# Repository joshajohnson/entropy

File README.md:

# Entropy

## A 96% Southpaw keyboard, with split space and encoder support. 

Entropy started as a STM32 powered keyboard running QMK and enclosed in a FR4 and PLA case, but at the time of writing runs on a nRF52 and ZMK, tucked inside a stacked acrylic case.

ZMK enables wireless functionality, and you'll get upwards of 6 months battery life thanks to the 200uA sleep current.

It also supports up to 4 rotary incoders in 5 different positions, along with a myriad of layout options.

## Photos

## Layout
Supports Encoders in (0,0)...(0,3) and (0,19)

ZMK versions only allow 4 encoders to be populated (hiting interrupt limit with 5 encoders)

## Revision History

R0.1: 
- Original STM32 design, no bugs that can't be worked around. 
- Tested and working.

R0.2: 
- Removed overengineering, modified to suit JLCSMT. 
- Fixed plate 2U tight fit. 
- **Has known issues with powering the LEDs, do not use**

### Image of R0.1 and R0.2 Design

R0.3: 

- Moved to nRF52840 and ZMK due to supply issues with the STM32F303 used in R0.1 and R0.2.
- Case design changed to plate mount in stacked acrylic case.
- Design moved to KiCad V6.

R0.4: 
- Battery life and design improvements over R0.3. 
- Few issues requiring rework but suitable for use.

R0.5: 
- Resolved issues found in R0.4, however untested. 
- **Use at your own risk.**

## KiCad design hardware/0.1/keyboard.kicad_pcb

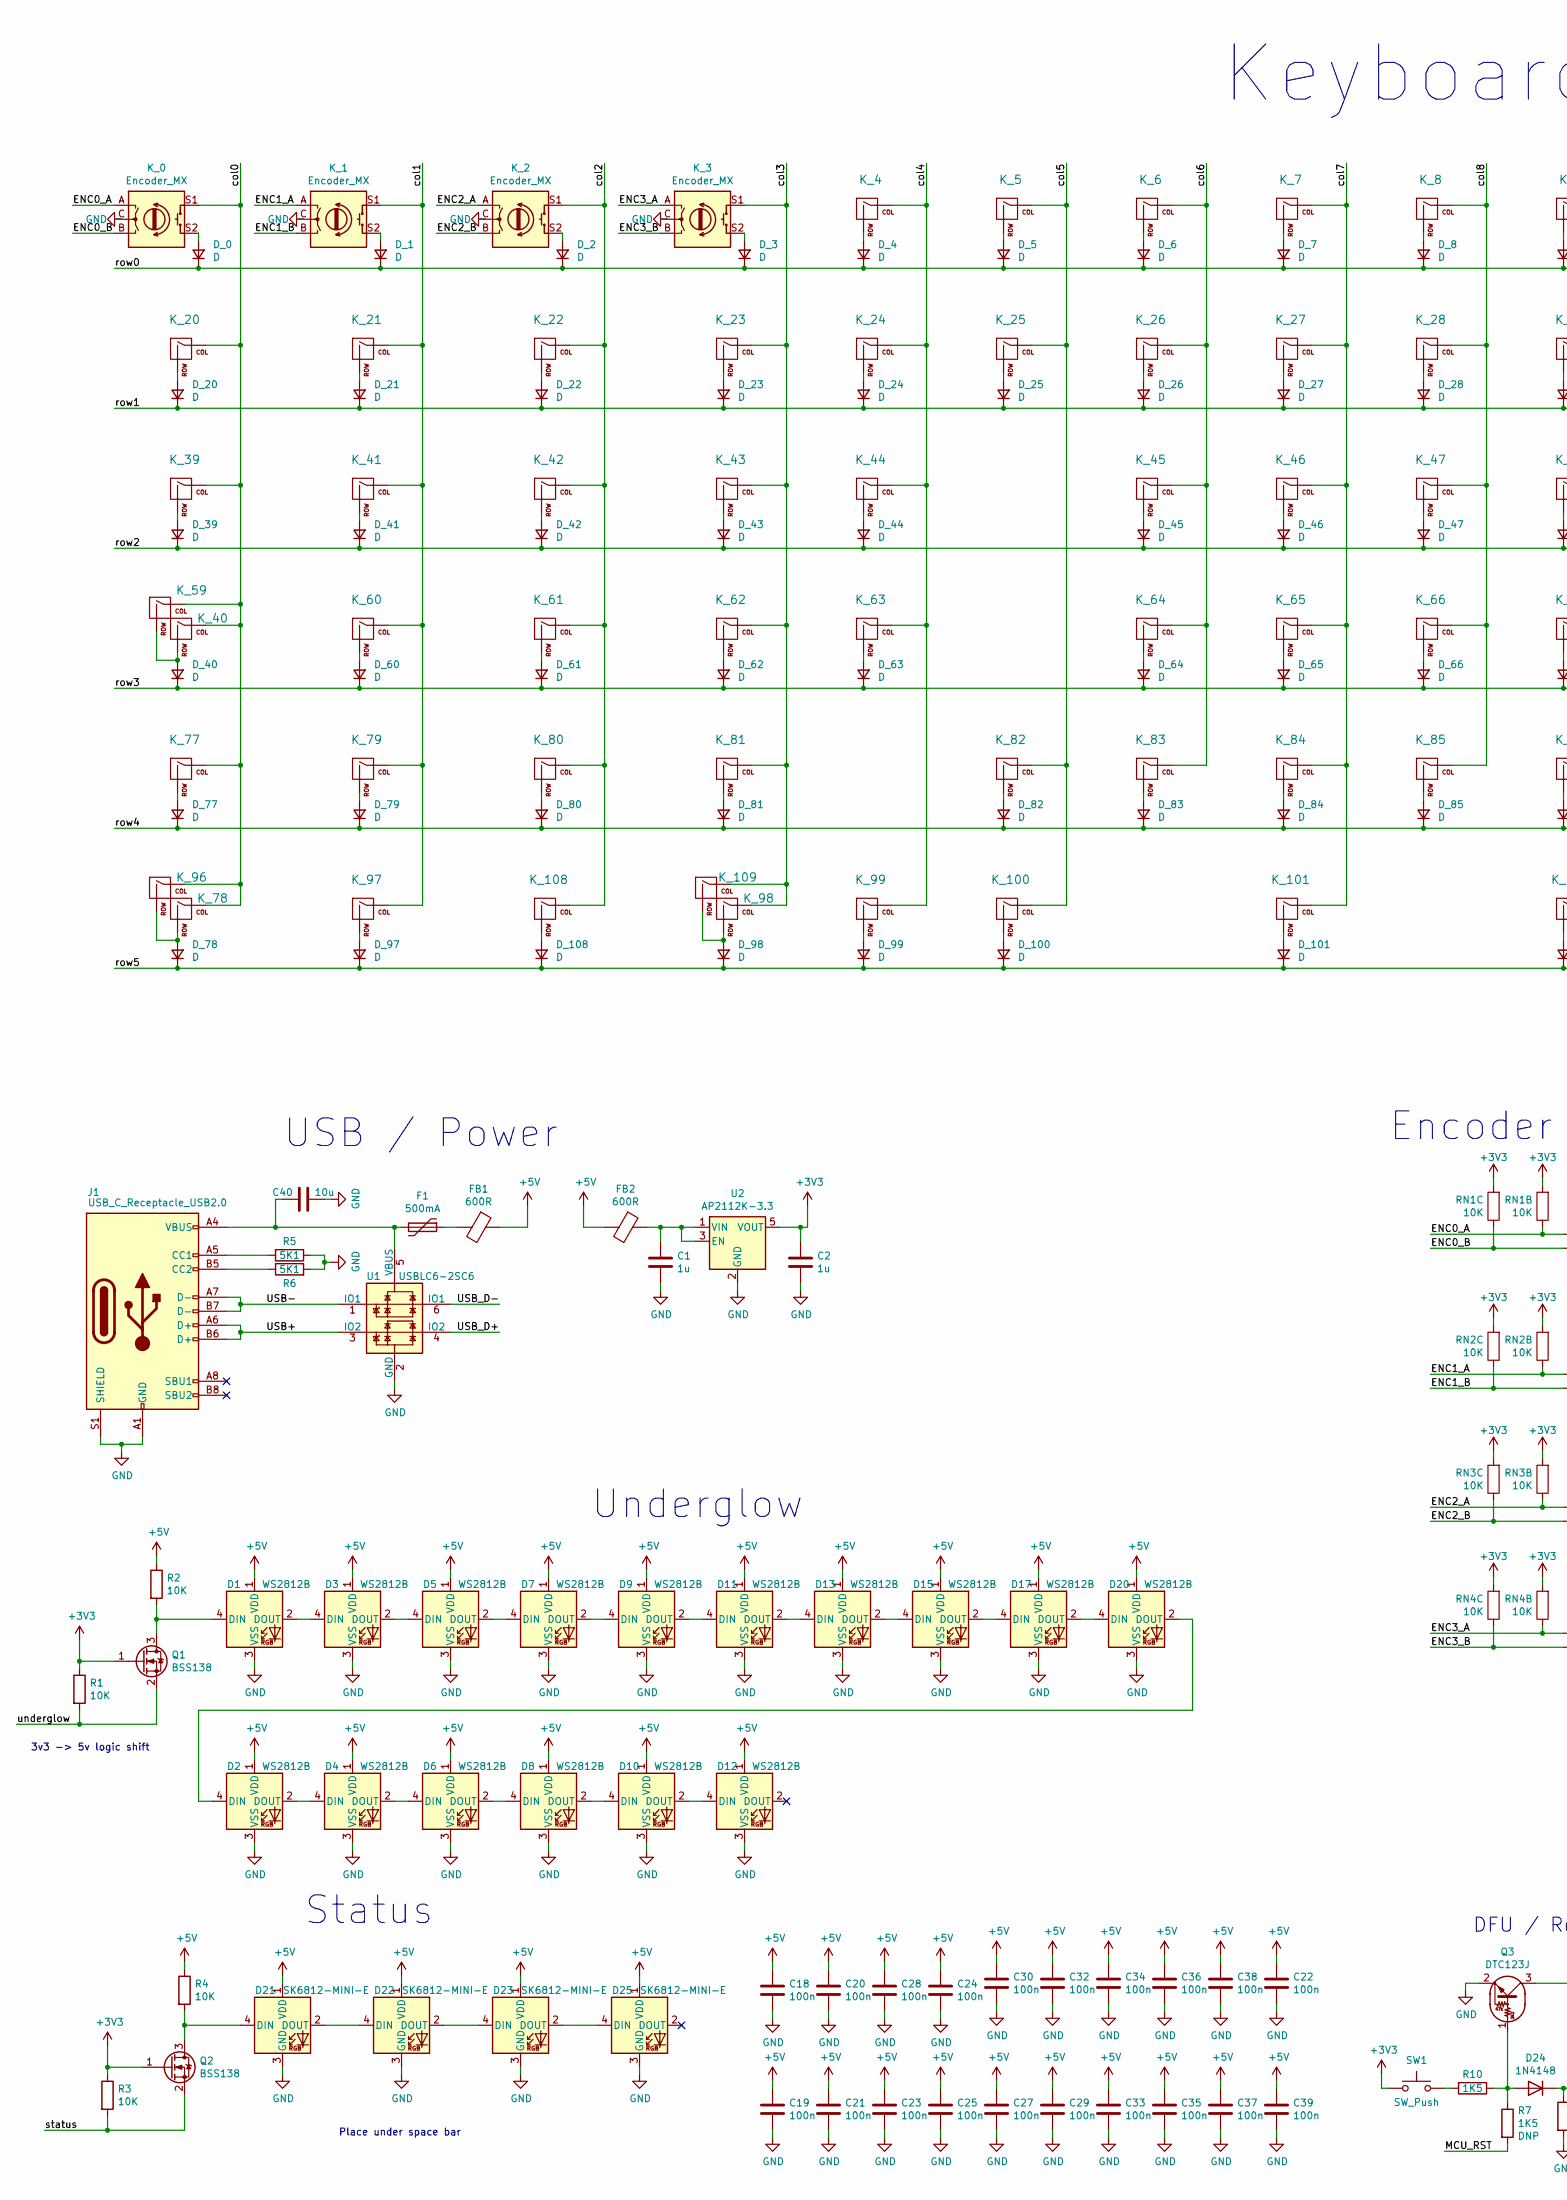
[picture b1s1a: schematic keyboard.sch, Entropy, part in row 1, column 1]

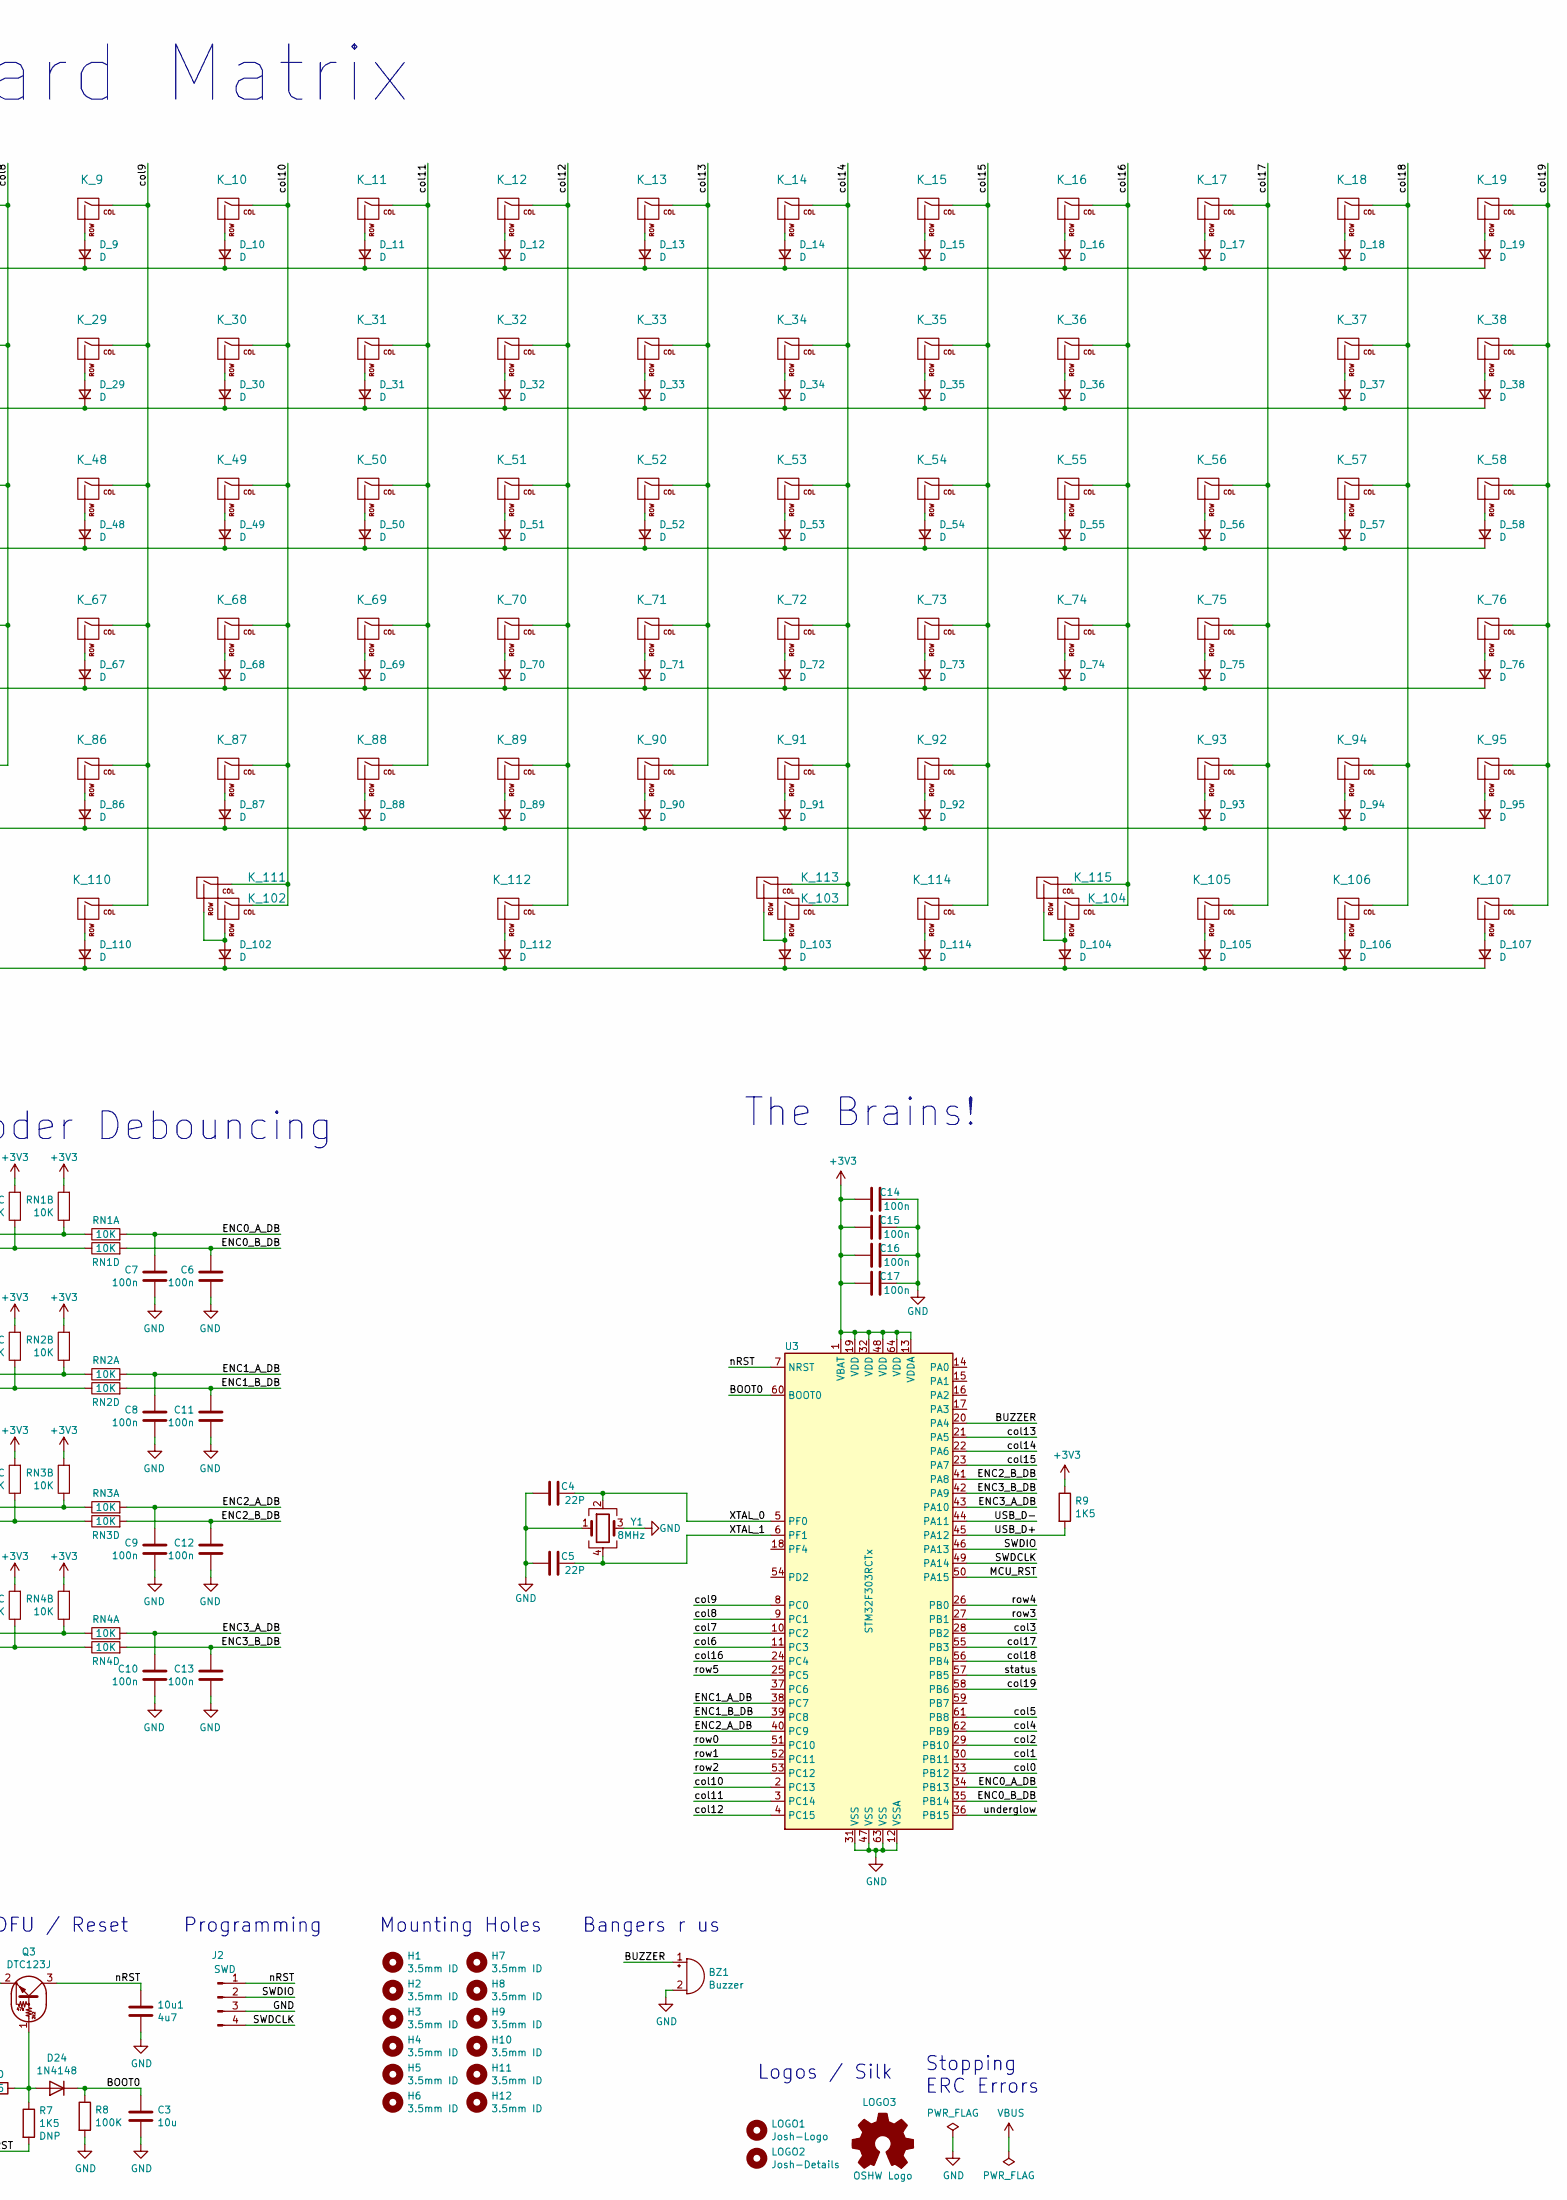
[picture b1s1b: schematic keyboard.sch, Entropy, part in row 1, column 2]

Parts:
10u1: 4u7; C_0603_1608Metric
BZ1: Buzzer; Buzzer_Murata_PKMCS0909E4000-R1
C1, C2: 1u; C_0603_1608Metric; MPN CL10A105MP8NNNC; LCSC C15849
C3, C40: 10u; C_0603_1608Metric
C4, C5: 22P; C_0603_1608Metric
C6, C7, C8, C9, C10, C11, C12, C13, C14, C15, C16, C17: 100n; C_0603_1608Metric
C18, C19, C20, C21, C22, C23, C24, C25, C27, C28, C29, C30, C32, C33, C34, C35, C36, C37, C38, C39: 100n; C_0603_1608Metric; MPN CL10A105MP8NNNC; LCSC C15849
D1, D2, D3, D4, D5, D6, D7, D8, D9, D10, D11, D12, D13, D15, D17, D20: WS2812B; LED_WS2812B_PLCC4_5.0x5.0mm_P3.2mm; MPN WS2812B-B; DigiKey 1528-1104-ND
D21, D22, D23, D25: SK6812-MINI-E; SK8612-MINI-E
D24: 1N4148; D_SOD-123
D_0, D_1, D_2, D_3, D_4, D_5, D_6, D_7, D_8, D_9, D_10, D_11, D_12, D_13, D_14, D_15, D_16, D_17, D_18, D_19, D_20, D_21, D_22, D_23, D_24, D_25, D_26, D_27, D_28, D_29, D_30, D_31, D_32, D_33, D_34, D_35, D_36, D_37, D_38, D_39, D_40, D_41, D_42, D_43, D_44, D_45, D_46, D_47, D_48, D_49, D_50, D_51, D_52, D_53, D_54, D_55, D_56, D_57, D_58, D_60, D_61, D_62, D_63, D_64, D_65, D_66, D_67, D_68, D_69, D_70, D_71, D_72, D_73, D_74, D_75, D_76, D_77, D_78, D_79, D_80, D_81, D_82, D_83, D_84, D_85, D_86, D_87, D_88, D_89, D_90, D_91, D_92, D_93, D_94, D_95, D_97, D_98, D_99, D_100, D_101, D_102, D_103, D_104, D_105, D_106, D_107, D_108, D_110, D_112, D_114: D; D_SOD-123
F1: 500mA; Fuse_0805_2012Metric
FB1, FB2: 600R; Ferrite_Bead_0603
H1, H2, H3, H4, H5, H6, H7, H8, H9, H10, H11, H12: 3.5mm ID; MountingHole_3.5mm
J1: USB_C_Receptacle_USB2.0; USB_C_U262-161N-4BVC11; MPN U262-161N-4BVC11; LCSC C319148
J2: SWD; STM_4_PIN_THT_Staggered
K_0, K_1, K_2, K_3: Encoder_MX; MX_KEYSWITCH_ENCODER
K_4, K_5, K_6, K_7, K_8, K_9, K_10, K_11, K_12, K_13, K_14, K_15, K_16, K_17, K_18, K_19, K_20, K_21, K_22, K_23, K_24, K_25, K_26, K_27, K_28, K_29, K_30, K_31, K_32, K_33, K_34, K_35, K_36, K_38, K_39, K_41, K_42, K_43, K_45, K_46, K_47, K_48, K_49, K_50, K_51, K_52, K_53, K_54, K_55, K_56, K_58, K_59, K_60, K_61, K_62, K_64, K_65, K_66, K_67, K_68, K_69, K_70, K_71, K_72, K_73, K_74, K_76, K_77, K_79, K_80, K_81, K_83, K_84, K_85, K_86, K_87, K_88, K_89, K_90, K_91, K_92, K_94, K_95, K_96, K_97, K_105, K_106, K_107, K_108, K_109, K_113, K_114, K_115: KEYSW; MXOnly-1U-NoLED
K_37, K_40, K_78: KEYSW; MXOnly-2U-NoLED
K_44, K_57, K_103, K_104: KEYSW; MXOnly-1.5U-NoLED
K_63, K_93: KEYSW; MXOnly-1.75U-NoLED
K_75, K_82, K_112: KEYSW; MXOnly-2.25U-ReversedStabilizers-NoLED
K_98: KEYSW; MXOnly-2U-ReversedStabilizers-NoLED
K_99, K_100, K_101, K_111: KEYSW; MXOnly-1.25U-NoLED
K_102: KEYSW; MXOnly-6.25U-ReversedStabilizers-NoLED
K_110: KEYSW; MXOnly-2.75U-ReversedStabilizers-NoLED
LOGO1: Josh-Logo; josh-johnson-logo-17x3
LOGO2: Josh-Details; josh-details
LOGO3: OSHW Logo; OSHW_Logo_3.6x3.6_F.Mask
Q1, Q2: BSS138; SOT-23; MPN BSS138P,215; LCSC C75547
Q3: DTC123J; SOT-23
R1, R2, R3, R4: 10K; R_0603_1608Metric; MPN CR0603-JW-103ELF; DigiKey CR0603-JW-103ELFCT-ND
R5, R6: 5K1; R_0603_1608Metric
R7, R9, R10: 1K5; R_0603_1608Metric
R8: 100K; R_0603_1608Metric
RN1, RN2, RN3, RN4: 10K; R_Array_Convex_4x0603
SW1: SW_Push; Panasonic_EVQPUL_EVQPUC
U1: USBLC6-2SC6; SOT-23-6
U2: AP2112K-3.3; SOT-23-5; MPN AP2112K-3.3TRG1; LCSC C51118
U3: STM32F303RCTx; LQFP-64_10x10mm_P0.5mm
Y1: 8MHz; Crystal_SMD_3225-4Pin_3.2x2.5mm

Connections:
+3V3: C2.2, C14.2, C15.2, C16.2, C17.2, Q1.1 (G), Q2.1 (G), R1.1, R3.1, R9.1, RN1.2, RN1.3, RN2.2, RN2.3, RN3.2, RN3.3, RN4.2, RN4.3, SW1.1, U2.5 (VOUT), U3.1 (VBAT), U3.13 (VDDA), U3.19 (VDD), U3.32 (VDD), U3.48 (VDD), U3.64 (VDD)
+5V: C18.2, C19.2, C20.2, C21.2, C22.2, C23.2, C24.2, C25.2, C27.2, C28.2, C29.2, C30.2, C32.2, C33.2, C34.2, C35.2, C36.2, C37.2, C38.2, C39.2, D1.1 (VDD), D2.1 (VDD), D3.1 (VDD), D4.1 (VDD), D5.1 (VDD), D6.1 (VDD), D7.1 (VDD), D8.1 (VDD), D9.1 (VDD), D10.1 (VDD), D11.1 (VDD), D12.1 (VDD), D13.1 (VDD), D15.1 (VDD), D17.1 (VDD), D20.1 (VDD), D21.1 (VDD), D22.1 (VDD), D23.1 (VDD), D25.1 (VDD), FB1.1, FB2.2, R2.1, R4.1
/BOOT0: C3.1, D24.1 (K), R8.1, U3.60 (BOOT0)
/BUZZER: BZ1.1 (-), U3.20 (PA4)
/ENC0_A: K_0.A, RN1.5, RN1.6
/ENC0_A_DB: C7.1, RN1.4, U3.34 (PB13)
/ENC0_B: K_0.B, RN1.7, RN1.8
/ENC0_B_DB: C6.1, RN1.1, U3.35 (PB14)
/ENC1_A: K_1.A, RN2.5, RN2.6
/ENC1_A_DB: C8.1, RN2.4, U3.38 (PC7)
/ENC1_B: K_1.B, RN2.7, RN2.8
/ENC1_B_DB: C11.1, RN2.1, U3.39 (PC8)
/ENC2_A: K_2.A, RN3.5, RN3.6
/ENC2_A_DB: C9.1, RN3.4, U3.40 (PC9)
/ENC2_B: K_2.B, RN3.7, RN3.8
/ENC2_B_DB: C12.1, RN3.1, U3.41 (PA8)
/ENC3_A: K_3.A, RN4.5, RN4.6
/ENC3_A_DB: C10.1, RN4.4, U3.43 (PA10)
/ENC3_B: K_3.B, RN4.7, RN4.8
/ENC3_B_DB: C13.1, RN4.1, U3.42 (PA9)
/MCU_RST: R7.2, U3.50 (PA15)
/SWDCLK: J2.4, U3.49 (PA14)
/SWDIO: J2.2, U3.46 (PA13)
/USB+: J1.A6 (D+), J1.B6 (D+), U1.3 (IO2)
/USB-: J1.A7 (D-), J1.B7 (D-), U1.1 (IO1)
/USB_D+: R9.2, U1.4 (IO2), U3.45 (PA12)
/USB_D-: U1.6 (IO1), U3.44 (PA11)
/XTAL_0: C4.1, U3.5 (PF0), Y1.2
/XTAL_1: C5.1, U3.6 (PF1), Y1.4
/col0: K_0.S1, K_20.1 (COL), K_39.1 (COL), K_40.1 (COL), K_59.1 (COL), K_77.1 (COL), K_78.1 (COL), K_96.1 (COL), U3.33 (PB12)
/col1: K_1.S1, K_21.1 (COL), K_41.1 (COL), K_60.1 (COL), K_79.1 (COL), K_97.1 (COL), U3.30 (PB11)
/col2: K_2.S1, K_22.1 (COL), K_42.1 (COL), K_61.1 (COL), K_80.1 (COL), K_108.1 (COL), U3.29 (PB10)
/col3: K_3.S1, K_23.1 (COL), K_43.1 (COL), K_62.1 (COL), K_81.1 (COL), K_98.1 (COL), K_109.1 (COL), U3.28 (PB2)
/col4: K_4.1 (COL), K_24.1 (COL), K_44.1 (COL), K_63.1 (COL), K_99.1 (COL), U3.62 (PB9)
/col5: K_5.1 (COL), K_25.1 (COL), K_82.1 (COL), K_100.1 (COL), U3.61 (PB8)
/col6: K_6.1 (COL), K_26.1 (COL), K_45.1 (COL), K_64.1 (COL), K_83.1 (COL), U3.11 (PC3)
/col7: K_7.1 (COL), K_27.1 (COL), K_46.1 (COL), K_65.1 (COL), K_84.1 (COL), K_101.1 (COL), U3.10 (PC2)
/col8: K_8.1 (COL), K_28.1 (COL), K_47.1 (COL), K_66.1 (COL), K_85.1 (COL), U3.9 (PC1)
/col9: K_9.1 (COL), K_29.1 (COL), K_48.1 (COL), K_67.1 (COL), K_86.1 (COL), K_110.1 (COL), U3.8 (PC0)
/col10: K_10.1 (COL), K_30.1 (COL), K_49.1 (COL), K_68.1 (COL), K_87.1 (COL), K_102.1 (COL), K_111.1 (COL), U3.2 (PC13)
/col11: K_11.1 (COL), K_31.1 (COL), K_50.1 (COL), K_69.1 (COL), K_88.1 (COL), U3.3 (PC14)
/col12: K_12.1 (COL), K_32.1 (COL), K_51.1 (COL), K_70.1 (COL), K_89.1 (COL), K_112.1 (COL), U3.4 (PC15)
/col13: K_13.1 (COL), K_33.1 (COL), K_52.1 (COL), K_71.1 (COL), K_90.1 (COL), U3.21 (PA5)
/col14: K_14.1 (COL), K_34.1 (COL), K_53.1 (COL), K_72.1 (COL), K_91.1 (COL), K_103.1 (COL), K_113.1 (COL), U3.22 (PA6)
/col15: K_15.1 (COL), K_35.1 (COL), K_54.1 (COL), K_73.1 (COL), K_92.1 (COL), K_114.1 (COL), U3.23 (PA7)
/col16: K_16.1 (COL), K_36.1 (COL), K_55.1 (COL), K_74.1 (COL), K_104.1 (COL), K_115.1 (COL), U3.24 (PC4)
/col17: K_17.1 (COL), K_56.1 (COL), K_75.1 (COL), K_93.1 (COL), K_105.1 (COL), U3.55 (PB3)
/col18: K_18.1 (COL), K_37.1 (COL), K_57.1 (COL), K_94.1 (COL), K_106.1 (COL), U3.56 (PB4)
/col19: K_19.1 (COL), K_38.1 (COL), K_58.1 (COL), K_76.1 (COL), K_95.1 (COL), K_107.1 (COL), U3.58 (PB6)
/nRST: 10u1.1, J2.1, Q3.3 (C), U3.7 (NRST)
/row0: D_0.1 (K), D_1.1 (K), D_2.1 (K), D_3.1 (K), D_4.1 (K), D_5.1 (K), D_6.1 (K), D_7.1 (K), D_8.1 (K), D_9.1 (K), D_10.1 (K), D_11.1 (K), D_12.1 (K), D_13.1 (K), D_14.1 (K), D_15.1 (K), D_16.1 (K), D_17.1 (K), D_18.1 (K), D_19.1 (K), U3.51 (PC10)
/row1: D_20.1 (K), D_21.1 (K), D_22.1 (K), D_23.1 (K), D_24.1 (K), D_25.1 (K), D_26.1 (K), D_27.1 (K), D_28.1 (K), D_29.1 (K), D_30.1 (K), D_31.1 (K), D_32.1 (K), D_33.1 (K), D_34.1 (K), D_35.1 (K), D_36.1 (K), D_37.1 (K), D_38.1 (K), U3.52 (PC11)
/row2: D_39.1 (K), D_41.1 (K), D_42.1 (K), D_43.1 (K), D_44.1 (K), D_45.1 (K), D_46.1 (K), D_47.1 (K), D_48.1 (K), D_49.1 (K), D_50.1 (K), D_51.1 (K), D_52.1 (K), D_53.1 (K), D_54.1 (K), D_55.1 (K), D_56.1 (K), D_57.1 (K), D_58.1 (K), U3.53 (PC12)
/row3: D_40.1 (K), D_60.1 (K), D_61.1 (K), D_62.1 (K), D_63.1 (K), D_64.1 (K), D_65.1 (K), D_66.1 (K), D_67.1 (K), D_68.1 (K), D_69.1 (K), D_70.1 (K), D_71.1 (K), D_72.1 (K), D_73.1 (K), D_74.1 (K), D_75.1 (K), D_76.1 (K), U3.27 (PB1)
/row4: D_77.1 (K), D_79.1 (K), D_80.1 (K), D_81.1 (K), D_82.1 (K), D_83.1 (K), D_84.1 (K), D_85.1 (K), D_86.1 (K), D_87.1 (K), D_88.1 (K), D_89.1 (K), D_90.1 (K), D_91.1 (K), D_92.1 (K), D_93.1 (K), D_94.1 (K), D_95.1 (K), U3.26 (PB0)
/row5: D_78.1 (K), D_97.1 (K), D_98.1 (K), D_99.1 (K), D_100.1 (K), D_101.1 (K), D_102.1 (K), D_103.1 (K), D_104.1 (K), D_105.1 (K), D_106.1 (K), D_107.1 (K), D_108.1 (K), D_110.1 (K), D_112.1 (K), D_114.1 (K), U3.25 (PC5)
/status: Q2.2 (S), R3.2, U3.57 (PB5)
/underglow: Q1.2 (S), R1.2, U3.36 (PB15)
GND: 10u1.2, BZ1.2 (+), C1.1, C2.1, C3.2, C4.2, C5.2, C6.2, C7.2, C8.2, C9.2, C10.2, C11.2, C12.2, C13.2, C14.1, C15.1, C16.1, C17.1, C18.1, C19.1, C20.1, C21.1, C22.1, C23.1, C24.1, C25.1, C27.1, C28.1, C29.1, C30.1, C32.1, C33.1, C34.1, C35.1, C36.1, C37.1, C38.1, C39.1, C40.1, D1.3 (VSS), D2.3 (VSS), D3.3 (VSS), D4.3 (VSS), D5.3 (VSS), D6.3 (VSS), D7.3 (VSS), D8.3 (VSS), D9.3 (VSS), D10.3 (VSS), D11.3 (VSS), D12.3 (VSS), D13.3 (VSS), D15.3 (VSS), D17.3 (VSS), D20.3 (VSS), D21.3 (GND), D22.3 (GND), D23.3 (GND), D25.3 (GND), J1.A1 (GND), J1.A12 (GND), J1.B1 (GND), J1.B12 (GND), J1.S1 (SHIELD), J2.3, K_0.C, K_1.C, K_2.C, K_3.C, Q3.2 (E), R5.1, R6.2, R8.2, U1.2 (GND), U2.2 (GND), U3.12 (VSSA), U3.31 (VSS), U3.47 (VSS), U3.63 (VSS), Y1.1, Y1.3
unnamed: C1.2, FB2.1, U2.1 (VIN), U2.3 (EN)
unnamed: C40.2, F1.2, J1.A4 (VBUS), J1.A9 (VBUS), J1.B4 (VBUS), J1.B9 (VBUS), U1.5 (VBUS)
unnamed: D1.2 (DOUT), D3.4 (DIN)
unnamed: D1.4 (DIN), Q1.3 (D), R2.2
unnamed: D2.2 (DOUT), D4.4 (DIN)
unnamed: D2.4 (DIN), D20.2 (DOUT)
unnamed: D3.2 (DOUT), D5.4 (DIN)
unnamed: D4.2 (DOUT), D6.4 (DIN)
unnamed: D5.2 (DOUT), D7.4 (DIN)
unnamed: D6.2 (DOUT), D8.4 (DIN)
unnamed: D7.2 (DOUT), D9.4 (DIN)
unnamed: D10.2 (DOUT), D12.4 (DIN)
unnamed: D8.2 (DOUT), D10.4 (DIN)
unnamed: D11.2 (DOUT), D13.4 (DIN)
unnamed: D9.2 (DOUT), D11.4 (DIN)
unnamed: D13.2 (DOUT), D15.4 (DIN)
unnamed: D15.2 (DOUT), D17.4 (DIN)
unnamed: D17.2 (DOUT), D20.4 (DIN)
unnamed: D21.2 (DOUT), D22.4 (DIN)
unnamed: D21.4 (DIN), Q2.3 (D), R4.2
unnamed: D22.2 (DOUT), D23.4 (DIN)
unnamed: D23.2 (DOUT), D25.4 (DIN)
unnamed: D24.2 (A), Q3.1 (B), R7.1, R10.1
unnamed: D_0.2 (A), K_0.S2
unnamed: D_1.2 (A), K_1.S2
unnamed: D_2.2 (A), K_2.S2
unnamed: D_3.2 (A), K_3.S2
unnamed: D_4.2 (A), K_4.2 (ROW)
unnamed: D_5.2 (A), K_5.2 (ROW)
unnamed: D_6.2 (A), K_6.2 (ROW)
unnamed: D_7.2 (A), K_7.2 (ROW)
unnamed: D_8.2 (A), K_8.2 (ROW)
unnamed: D_9.2 (A), K_9.2 (ROW)
unnamed: D_10.2 (A), K_10.2 (ROW)
unnamed: D_11.2 (A), K_11.2 (ROW)
unnamed: D_12.2 (A), K_12.2 (ROW)
unnamed: D_13.2 (A), K_13.2 (ROW)
unnamed: D_14.2 (A), K_14.2 (ROW)
unnamed: D_15.2 (A), K_15.2 (ROW)
unnamed: D_16.2 (A), K_16.2 (ROW)
unnamed: D_17.2 (A), K_17.2 (ROW)
unnamed: D_18.2 (A), K_18.2 (ROW)
unnamed: D_19.2 (A), K_19.2 (ROW)
unnamed: D_20.2 (A), K_20.2 (ROW)
unnamed: D_21.2 (A), K_21.2 (ROW)
unnamed: D_22.2 (A), K_22.2 (ROW)
unnamed: D_23.2 (A), K_23.2 (ROW)
unnamed: D_24.2 (A), K_24.2 (ROW)
unnamed: D_25.2 (A), K_25.2 (ROW)
unnamed: D_26.2 (A), K_26.2 (ROW)
unnamed: D_27.2 (A), K_27.2 (ROW)
unnamed: D_28.2 (A), K_28.2 (ROW)
unnamed: D_29.2 (A), K_29.2 (ROW)
unnamed: D_30.2 (A), K_30.2 (ROW)
unnamed: D_31.2 (A), K_31.2 (ROW)
unnamed: D_32.2 (A), K_32.2 (ROW)
unnamed: D_33.2 (A), K_33.2 (ROW)
unnamed: D_34.2 (A), K_34.2 (ROW)
unnamed: D_35.2 (A), K_35.2 (ROW)
unnamed: D_36.2 (A), K_36.2 (ROW)
unnamed: D_37.2 (A), K_37.2 (ROW)
unnamed: D_38.2 (A), K_38.2 (ROW)
unnamed: D_39.2 (A), K_39.2 (ROW)
unnamed: D_40.2 (A), K_40.2 (ROW), K_59.2 (ROW)
unnamed: D_41.2 (A), K_41.2 (ROW)
unnamed: D_42.2 (A), K_42.2 (ROW)
unnamed: D_43.2 (A), K_43.2 (ROW)
unnamed: D_44.2 (A), K_44.2 (ROW)
unnamed: D_45.2 (A), K_45.2 (ROW)
unnamed: D_46.2 (A), K_46.2 (ROW)
unnamed: D_47.2 (A), K_47.2 (ROW)
unnamed: D_48.2 (A), K_48.2 (ROW)
unnamed: D_49.2 (A), K_49.2 (ROW)
unnamed: D_50.2 (A), K_50.2 (ROW)
unnamed: D_51.2 (A), K_51.2 (ROW)
unnamed: D_52.2 (A), K_52.2 (ROW)
unnamed: D_53.2 (A), K_53.2 (ROW)
unnamed: D_54.2 (A), K_54.2 (ROW)
unnamed: D_55.2 (A), K_55.2 (ROW)
unnamed: D_56.2 (A), K_56.2 (ROW)
unnamed: D_57.2 (A), K_57.2 (ROW)
unnamed: D_58.2 (A), K_58.2 (ROW)
unnamed: D_60.2 (A), K_60.2 (ROW)
unnamed: D_61.2 (A), K_61.2 (ROW)
unnamed: D_62.2 (A), K_62.2 (ROW)
unnamed: D_63.2 (A), K_63.2 (ROW)
unnamed: D_64.2 (A), K_64.2 (ROW)
unnamed: D_65.2 (A), K_65.2 (ROW)
unnamed: D_66.2 (A), K_66.2 (ROW)
unnamed: D_67.2 (A), K_67.2 (ROW)
unnamed: D_68.2 (A), K_68.2 (ROW)
unnamed: D_69.2 (A), K_69.2 (ROW)
unnamed: D_70.2 (A), K_70.2 (ROW)
unnamed: D_71.2 (A), K_71.2 (ROW)
unnamed: D_72.2 (A), K_72.2 (ROW)
unnamed: D_73.2 (A), K_73.2 (ROW)
unnamed: D_74.2 (A), K_74.2 (ROW)
unnamed: D_75.2 (A), K_75.2 (ROW)
unnamed: D_76.2 (A), K_76.2 (ROW)
unnamed: D_77.2 (A), K_77.2 (ROW)
unnamed: D_78.2 (A), K_78.2 (ROW), K_96.2 (ROW)
unnamed: D_79.2 (A), K_79.2 (ROW)
unnamed: D_80.2 (A), K_80.2 (ROW)
unnamed: D_81.2 (A), K_81.2 (ROW)
unnamed: D_82.2 (A), K_82.2 (ROW)
unnamed: D_83.2 (A), K_83.2 (ROW)
unnamed: D_84.2 (A), K_84.2 (ROW)
unnamed: D_85.2 (A), K_85.2 (ROW)
unnamed: D_86.2 (A), K_86.2 (ROW)
unnamed: D_87.2 (A), K_87.2 (ROW)
unnamed: D_88.2 (A), K_88.2 (ROW)
unnamed: D_89.2 (A), K_89.2 (ROW)
unnamed: D_90.2 (A), K_90.2 (ROW)
unnamed: D_91.2 (A), K_91.2 (ROW)
unnamed: D_92.2 (A), K_92.2 (ROW)
unnamed: D_93.2 (A), K_93.2 (ROW)
unnamed: D_94.2 (A), K_94.2 (ROW)
unnamed: D_95.2 (A), K_95.2 (ROW)
unnamed: D_97.2 (A), K_97.2 (ROW)
unnamed: D_98.2 (A), K_98.2 (ROW), K_109.2 (ROW)
unnamed: D_99.2 (A), K_99.2 (ROW)
unnamed: D_100.2 (A), K_100.2 (ROW)
unnamed: D_101.2 (A), K_101.2 (ROW)
unnamed: D_102.2 (A), K_102.2 (ROW), K_111.2 (ROW)
unnamed: D_103.2 (A), K_103.2 (ROW), K_113.2 (ROW)
unnamed: D_104.2 (A), K_104.2 (ROW), K_115.2 (ROW)
unnamed: D_105.2 (A), K_105.2 (ROW)
unnamed: D_106.2 (A), K_106.2 (ROW)
unnamed: D_107.2 (A), K_107.2 (ROW)
unnamed: D_108.2 (A), K_108.2 (ROW)
unnamed: D_110.2 (A), K_110.2 (ROW)
unnamed: D_112.2 (A), K_112.2 (ROW)
unnamed: D_114.2 (A), K_114.2 (ROW)
unnamed: F1.1, FB1.2
unnamed: J1.A5 (CC1), R5.2
unnamed: J1.B5 (CC2), R6.1
unnamed: R10.2, SW1.2

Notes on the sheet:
Stopping ERC Errors
Underglow
3v3 -> 5v logic shift
Logos / Silk
Keyboard Matrix
Status
DFU / Reset
Place under space bar
USB / Power
Programming
Encoder Debouncing
The Brains!
Mounting Holes
Bangers r us

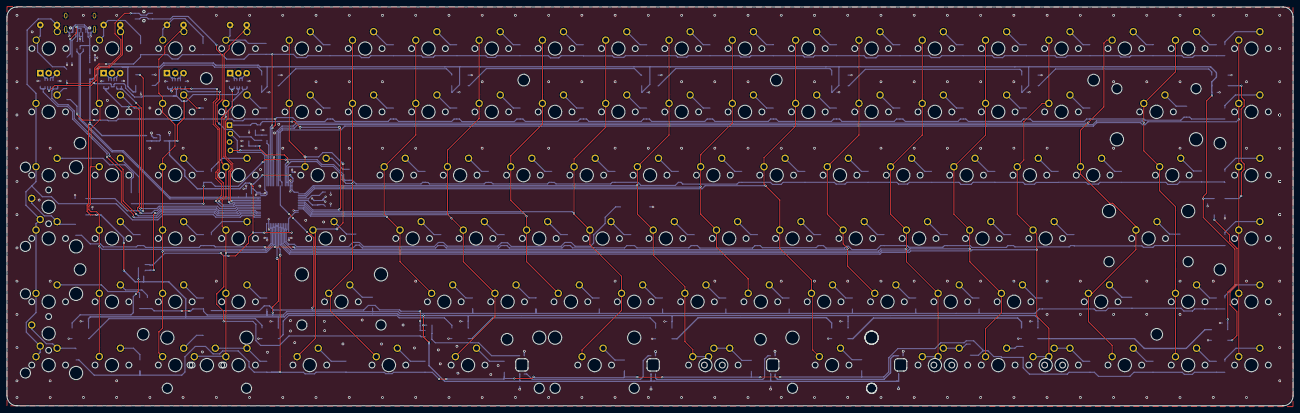
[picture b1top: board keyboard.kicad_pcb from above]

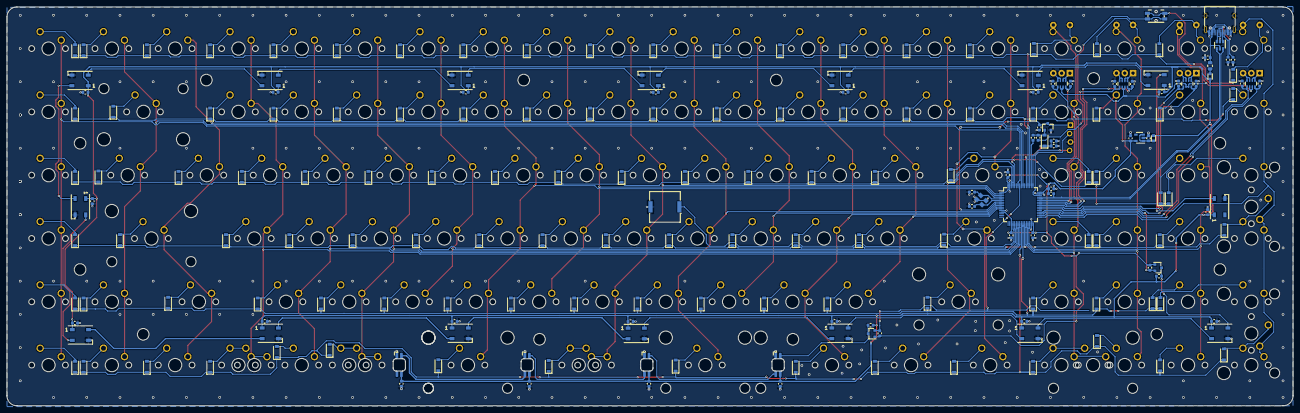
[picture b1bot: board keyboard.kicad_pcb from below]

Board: 2 copper layers, 387.0 x 120.0 mm, 329 parts (197 on the bottom side), 196 nets.

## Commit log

2020-06-08 init, almost finished placing compenents
2020-06-08 continuing layout
2020-06-08 change name
2020-06-09 layout ++
2020-06-11 unrouted = 0 with no matrix - mcu connections
2020-06-13 layout done
2020-06-14 graphics added
2020-06-14 updated 3d model
2020-06-14 partial upper plate done
2020-06-14 update mounting hole locations
2020-06-14 mechanical changes
2020-06-17 merged LEDs into one string
2020-06-20 cleaning up schematic
2020-06-21 add encoder top right
2020-06-25 add split backspace
2020-07-03 dunno
2020-07-07 off to fab
2020-07-26 add images to readme
2020-12-25 r0.2 release, untested. Add firmware + VIA files
2020-12-25 add stl for case
2020-12-25 add f3d
2021-04-17 begun work on 0.3w
2021-04-18 all parts placed
2021-04-23 drc = erc = 0
2021-04-25 added user led
2021-04-25 added updated plate
2021-04-28 clean up layout
2021-04-28 updated plate cutout for 3mm acrylic
2021-07-25 finalise 0.3w
2021-07-25 0.4 first pass layout done
2021-07-25 0.4w WIP layout
2021-07-26 clean up routing
2021-12-18 0.4 cleanup and 0.5 addition of files
2021-12-18 update kle
2021-12-19 add photos
